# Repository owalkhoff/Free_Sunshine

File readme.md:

# Free Sunshine!

Promoting mechatronic art & sustainable energy in South Africa one g☼ggab☼t at a time

## What is this project about?

It is about spreading access to and an interest in electronics and art.

It also raises awareness about sustainable energy and the current development in South Africa of legislation regarding small scale solar energy generators. The project is driven by Miranda Moss and Oliver Walkhoff and is made possible with the support of the Swiss Arts Council Pro Helvetia. Find out more on the project website:

[freesunshine.org](http://freesunshine.org)

## What is a g☼ggab☼t?

A g☼ggab☼t is a small solar-powered robot. About 200 of them have been built in workshops during ISEA 2018, Durban, and subsequently at Baleni Senior Secondary School, Kwazulu Natal, South Africa.

A g☼ggab☼t consists of a printed circuit board (pcb), one or two solar cells, a motor, a capacitor and some mechanical parts. For the workshops, the pcb was pre-populated with smd components. The participants soldered the larger components to the board and added bristles, wire, beads and other things to create their individual bot.

## How can I build my own g☼ggab☼t?

We have created a pamphlet with a short description of the parts and some building instructions:

[Pamphlet in English](pdf/goggabot_pamphlet_english.pdf)

[Pamphlet in Zulu](pdf/goggabot_pamphlet_zulu.pdf)

## How does the circuit work?

A schematic and a short description of the g☼ggab☼t circuit is also on the pamphlet. It was contributed by Uwe Schüler of Kulturgüter-Schuppen, Dusslingen, Germany.

[www.kulturgueter-schuppen.de](http://www.kulturgueter-schuppen.de)

## How was the pcb made?

The pcb was created using KiCad Version 4.0.7. The boards were manufactured by PCBWay in China, and assembled by R2 Manufacturing, Glattbrugg, Switzerland.

The KiCad and Gerber files which were used for production can be found [in this repository](goggabot).

This is a rendering of the front, with components:

And here is the back:

## License

The g☼ggab☼t circuit is CC NC BY kulturgueter-schuppen.de.

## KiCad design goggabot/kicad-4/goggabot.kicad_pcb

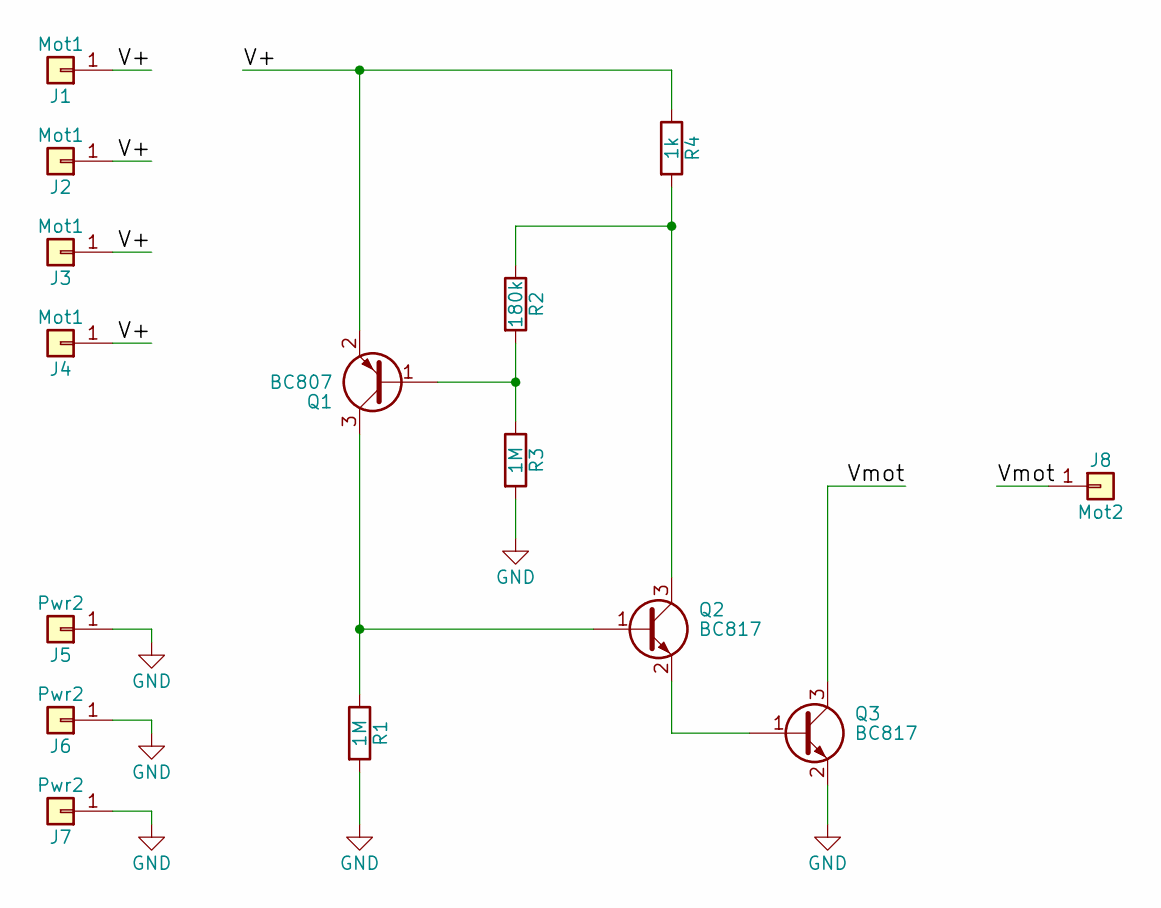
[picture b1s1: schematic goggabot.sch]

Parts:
J1, J2, J3, J4: Mot1; Socket_Strip_Straight_1x01
J5, J6, J7: Pwr2; Socket_Strip_Straight_1x01
J8: Mot2; Socket_Strip_Straight_1x01
Q1: BC807; SOT-23
Q2, Q3: BC817; SOT-23
R1, R3: 1M; R_1206_HandSoldering
R2: 180k; R_1206_HandSoldering
R4: 1k; R_1206_HandSoldering

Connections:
/V+: J1.1, J2.1, J3.1, J4.1, Q1.2 (E), R4.1
/Vmot: J8.1, Q3.3 (C)
GND: J5.1, J6.1, J7.1, Q3.2 (E), R1.2, R3.2
unnamed: Q1.1 (B), R2.2, R3.1
unnamed: Q1.3 (C), Q2.1 (B), R1.1
unnamed: Q2.2 (E), Q3.1 (B)
unnamed: Q2.3 (C), R2.1, R4.2

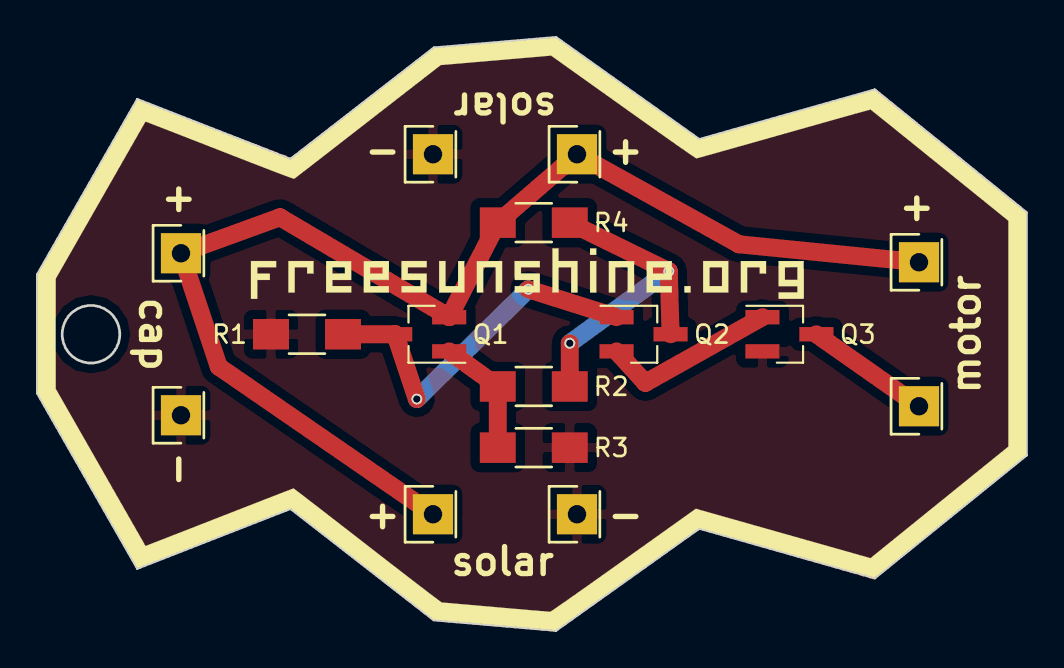
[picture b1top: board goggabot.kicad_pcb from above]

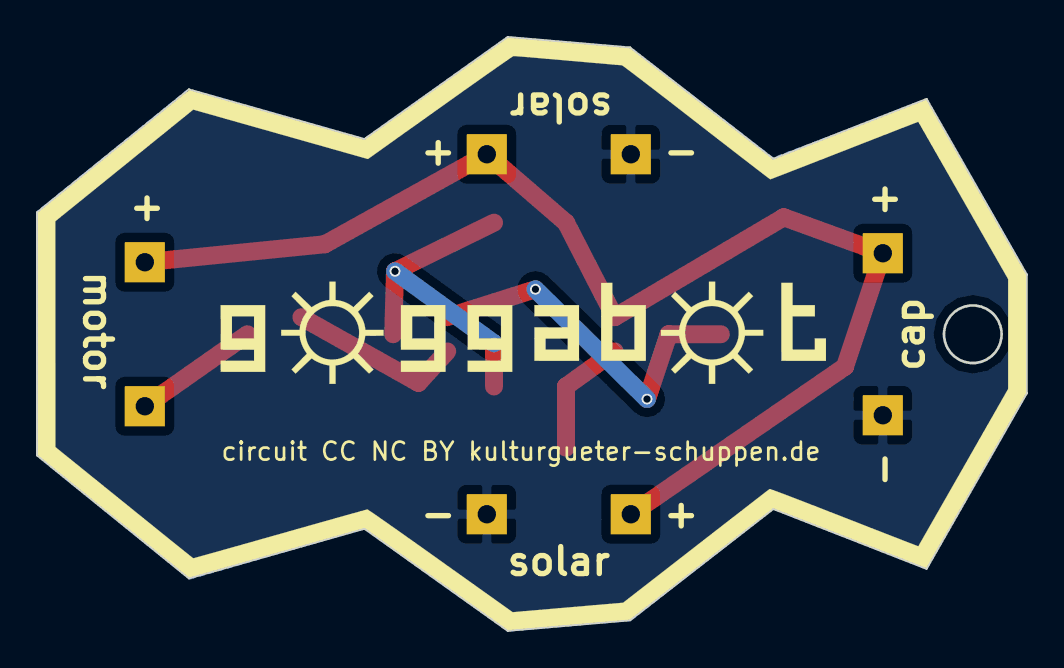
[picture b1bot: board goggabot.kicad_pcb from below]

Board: 2 copper layers, 54.9 x 32.9 mm, 21 parts (3 on the bottom side), 7 nets.

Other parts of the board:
freesunshine: LOGO; goggabot_freesunshine_31x3
goggabot: LOGO; goggabot_logo_34x6
mask: LOGO; goggabot_55x33_mask
mask#2: LOGO; goggabot_55x33_mask
outline: LOGO; goggabot_55x33_outline_1mm
outline#2: LOGO; goggabot_55x33_outline_1mm

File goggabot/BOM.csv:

Resistor,R1,1M,R_1206
Resistor,R2,180k,R_1206
Resistor,R3,1M,R_1206
Resistor,R4,1k,R_1206
Transistor,Q1,BC807,SOT-23
Transistor,Q2,BC817,SOT-23
Transistor,Q3,BC817,SOT-23

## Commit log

2018-08-17 Initial commit
    Start documenting Free Sunshine!
2018-08-17 Add KiCad and Gerber files
    These were used for production. Made with KiCad 4.0.7.
2018-08-17 Add images, update readme
2018-08-17 Add english pamphlet
2018-08-17 Add zulu pamphlet, update readme
2018-08-17 Add BOM
